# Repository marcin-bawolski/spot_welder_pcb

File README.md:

# spot_welder_pcb
PCB for STM8S based timer to control spot welder in KiCAD format.

Board using STM8s module and four digit 7-seg LED display as timer in 999 ms range.
Used as timer for spot-welding by triggering triac and large transformer.

uses sch and cb libraries from https://github.com/marcin-bawolski/kicad-libs.git

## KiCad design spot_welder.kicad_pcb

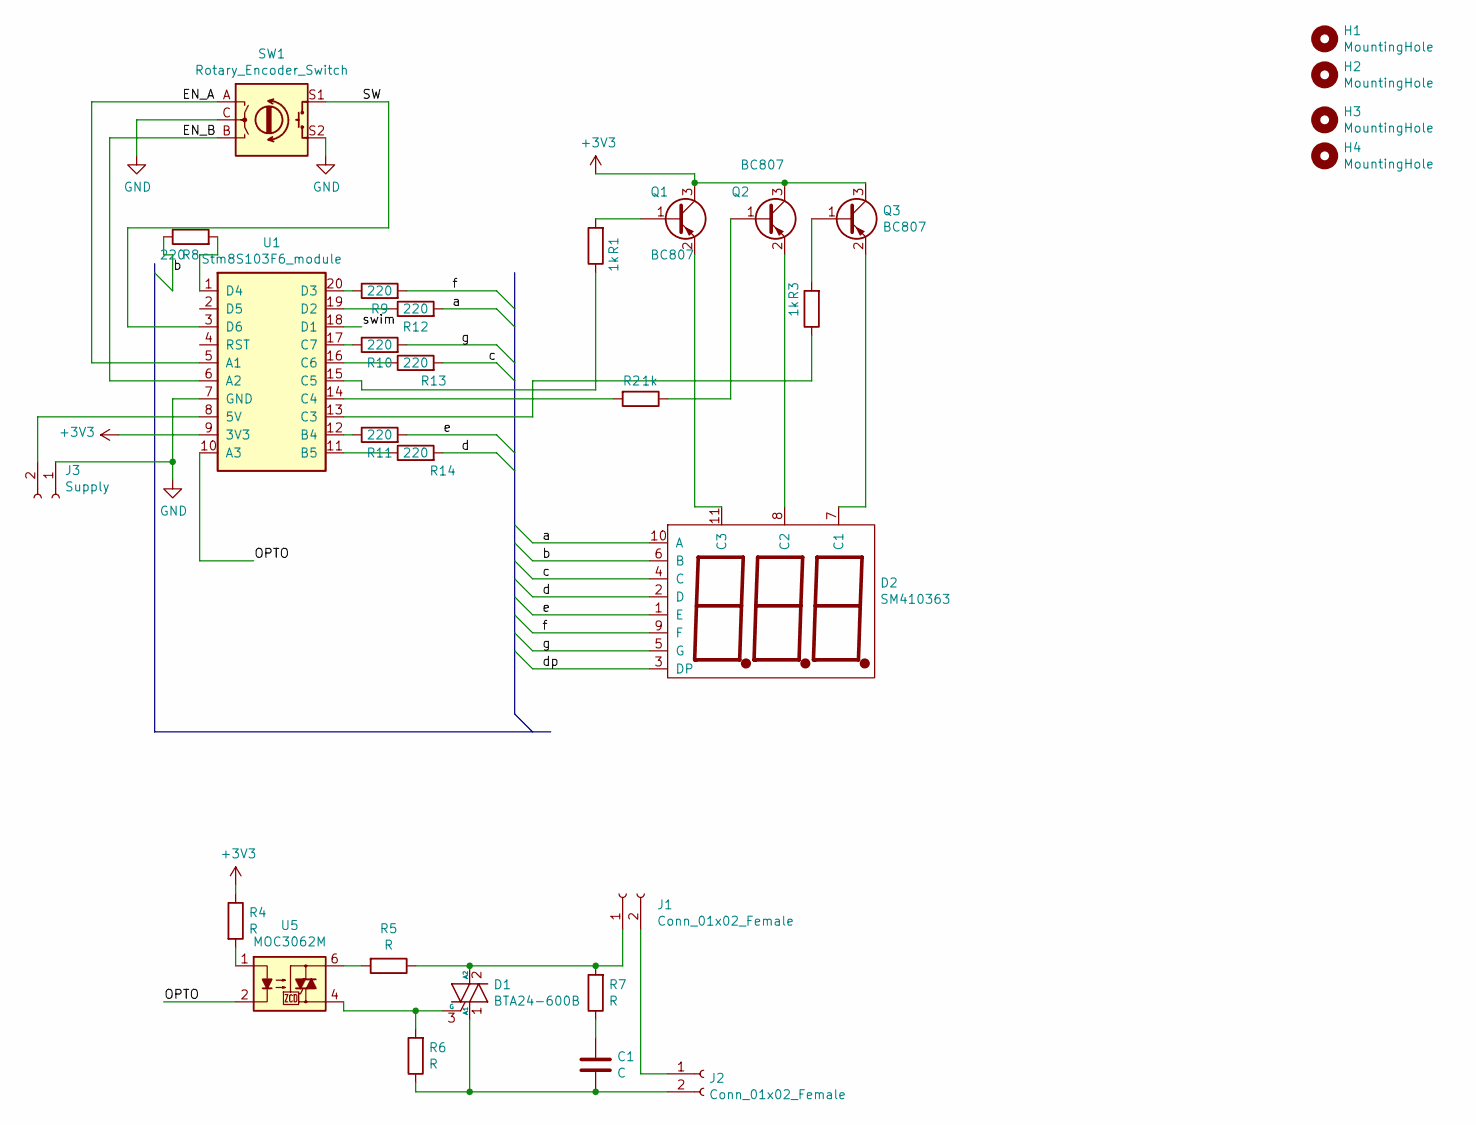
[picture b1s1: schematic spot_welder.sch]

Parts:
C1: C; C_Rect_L13.0mm_W3.0mm_P10.00mm_FKS3_FKP3_MKS4
D1: BTA24-600B; TO-220-3_Vertical
D2: SM410363
H1, H2, H3, H4: MountingHole; MountingHole_3.2mm_M3_DIN965_Pad
J1, J2: Conn_01x02_Female; PhoenixContact_GMSTBVA_2,5_2-G-7,62_1x02_P7.62mm_Vertical
J3: Supply; PhoenixContact_GMSTBVA_2,5_2-G-7,62_1x02_P7.62mm_Vertical
Q1, Q2, Q3: BC807; SOT-23
R1, R2, R3: 1k; R_0805_2012Metric_Pad1.15x1.40mm_HandSolder
R4: R; R_0805_2012Metric
R5, R6, R7: R; R_Axial_DIN0207_L6.3mm_D2.5mm_P10.16mm_Horizontal
R8, R9, R10, R11, R12, R13, R14: 220; R_0805_2012Metric_Pad1.15x1.40mm_HandSolder
SW1: Rotary_Encoder_Switch; RotaryEncoder_Alps_EC12E-Switch_Vertical_H20mm_CircularMoun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
U1: Stm8S103F6_module; DIP-20_600_ELL
U5: MOC3062M; DIP-6_W7.62mm_LongPads

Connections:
+3V3: Q1.3 (C), Q2.3 (C), Q3.3 (C), R4.1, U1.9 (3V3)
/EN_A: SW1.A, U1.5 (A1)
/EN_B: SW1.B, U1.6 (A2)
/OPTO: U1.10 (A3), U5.2
/SW: SW1.S1, U1.3 (D6)
/a: D2.10 (A), R12.2
/b: D2.6 (B), R8.1
/c: D2.4 (C), R13.2
/d: D2.2 (D), R14.2
/dp: D2.3 (DP)
/e: D2.1 (E), R11.2
/f: D2.9 (F), R9.2
/g: D2.5 (G), R10.2
/swim: U1.18 (D1)
GND: J3.1, SW1.C, SW1.S2, U1.7 (GND)
unnamed: C1.1, R7.1
unnamed: C1.2, D1.1 (A1), J2.2, R6.1
unnamed: D1.2 (A2), J1.1, R5.1, R7.2
unnamed: D1.3 (G), R6.2, U5.4
unnamed: D2.7 (C1), Q3.2 (E)
unnamed: D2.8 (C2), Q2.2 (E)
unnamed: D2.11 (C3), Q1.2 (E)
unnamed: J1.2, J2.1
unnamed: J3.2, U1.8 (5V)
unnamed: Q1.1 (B), R1.2
unnamed: Q2.1 (B), R2.1
unnamed: Q3.1 (B), R3.2
unnamed: R1.1, U1.15 (C5)
unnamed: R2.2, U1.14 (C4)
unnamed: R3.1, U1.13 (C3)
unnamed: R4.2, U5.1
unnamed: R5.2, U5.6
unnamed: R8.2, U1.1 (D4)
unnamed: R9.1, U1.20 (D3)
unnamed: R10.1, U1.17 (C7)
unnamed: R11.1, U1.12 (B4)
unnamed: R12.1, U1.19 (D2)
unnamed: R13.1, U1.16 (C6)
unnamed: R14.1, U1.11 (B5)

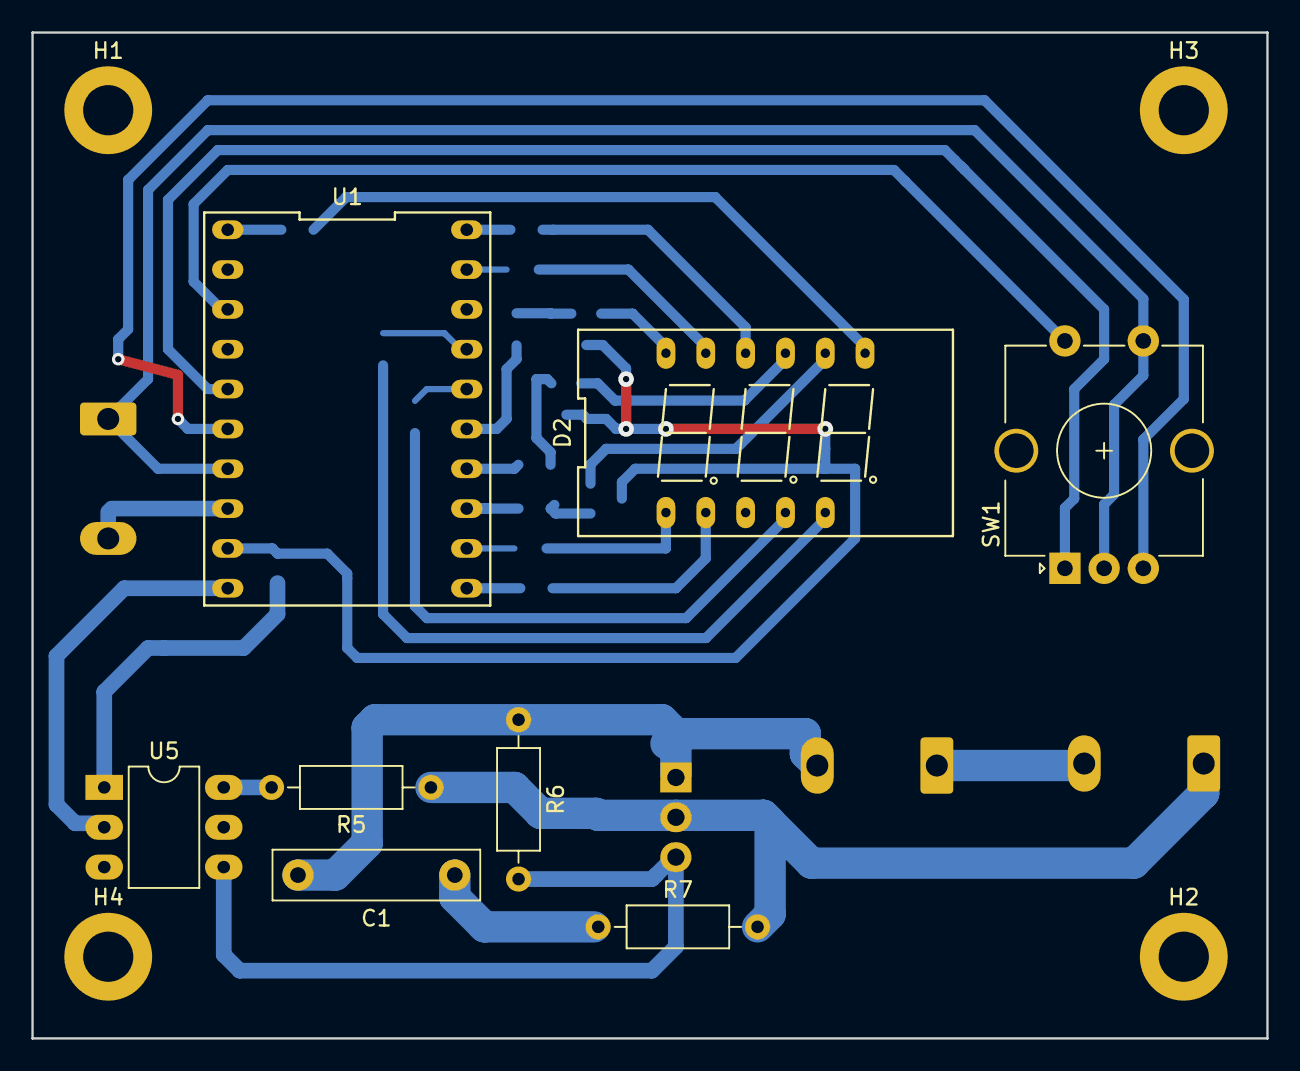
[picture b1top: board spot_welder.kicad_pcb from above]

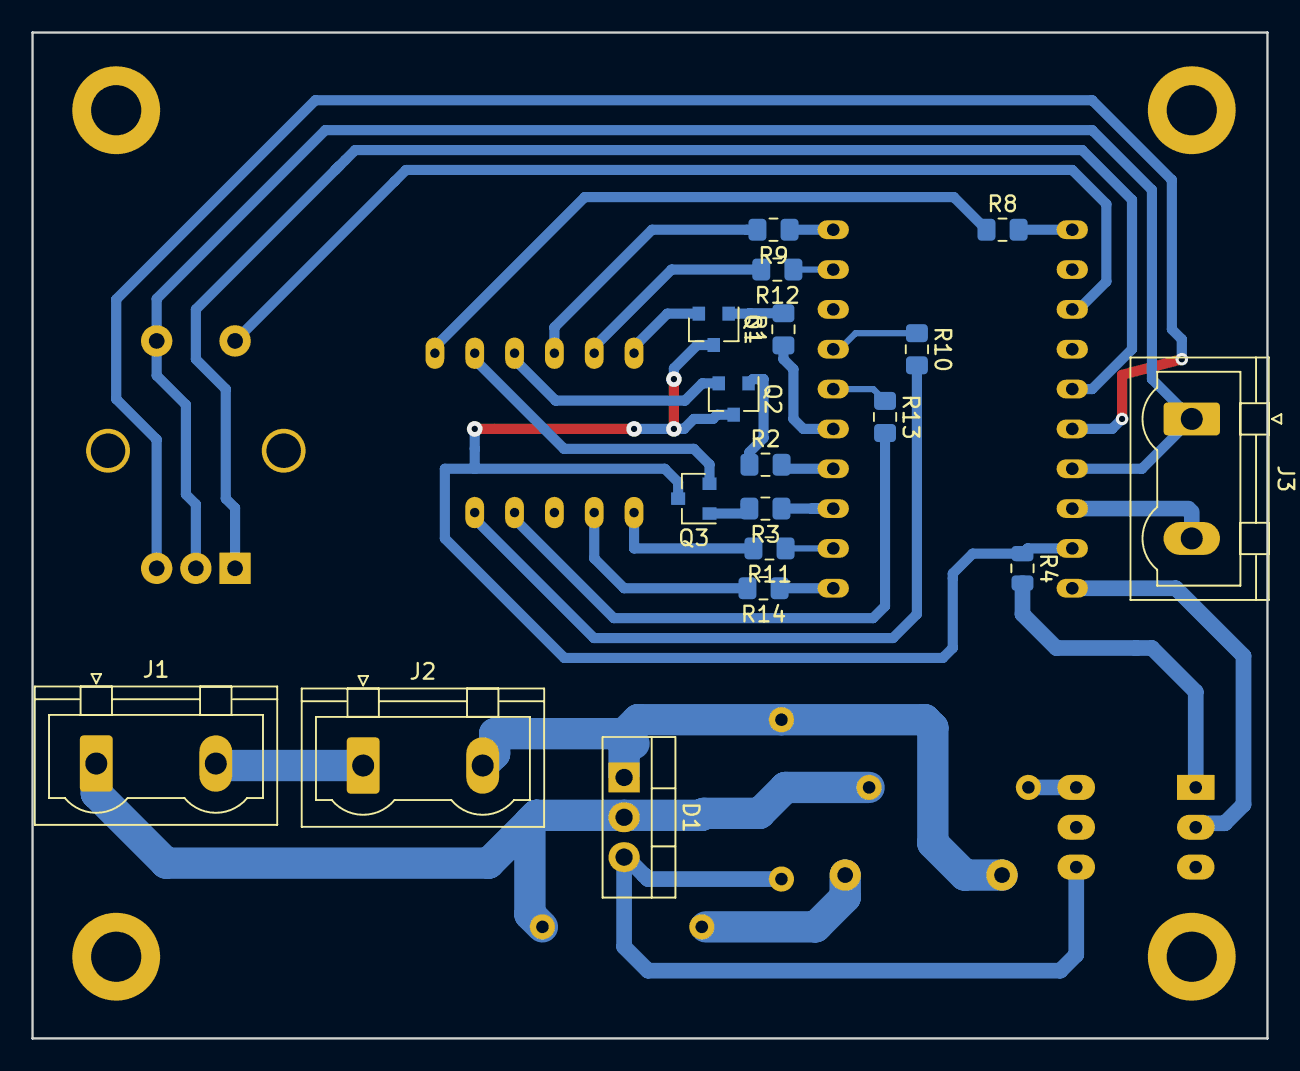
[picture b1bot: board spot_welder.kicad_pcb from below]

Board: 2 copper layers, 78.7 x 64.1 mm, 30 parts (18 on the bottom side), 37 nets.

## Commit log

2020-06-19 Swapped display of 100 and 1
2020-06-19 stm8 module footprint changed
2020-06-19 mounting holes added
2020-06-19 Add segment resistors
2020-06-19 encoder moved to right of display
2020-06-23 3x7seg LED module
2020-06-23 HV part at bottom of PCB
2020-07-01 clearances increased, vias enlarged
2020-11-27 Fabricated version
2023-02-22 library name updated
2023-02-22 Updared readme with library location
